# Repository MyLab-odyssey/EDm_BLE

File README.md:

# EDm_BLE

Monitor the status of your Smart electric drive EV with the Blynk app.  
**This is a work-in-progress project - more features to come...**

Further documentation in the [Wiki](https://github.com/MyLab-odyssey/EDm_BLE/wiki).

---
## Intention
When driving your electric car the knowledge of the real state of charge (SoC) is essential. The usable range is directly related to the SoC of the battery. Some EVs - like the Smart ED - will hide some Ah for back-up and the displayed SoC is more pessimistic than the real charge would suggest.

In the [ED_BMSdiag project](https://github.com/MyLab-odyssey/ED_BMSdiag) I developed a diagnostics tool for the Smart electric drive EV based on an Arduino UNO with a CAN bus shield. Data is send via a serial USB connection to a laptop.  
In every day use this is not a practical use case, so I searched for an easy solution to display the data on a mobile phone. [The Blynk app](http://www.blynk.cc) is a great way for a very flexible dashboard on iOS and on Android phones.

<p align="center">

<p/>

You can display the content you need and arrange different widgets to show the values. Using gauges, value displays and graphs the app gives you the freedom to select the data you really need.

<p align="center">

<br>
(rearrange widgets or add a graph)<br>
<p/>

Blynk is able to use a bluetooth low energy connection for data transmission. But adding a BLE interface to the Arduino would be only a small step forward. So I decided to develop my own BLE dongle to connect to the OBD port of the car. A system I can leave plugged in while driving and to be energy efficient to stay without depleting the 12V battery. Therefor the RFduino micro controller is the perfect fit as it is small, very efficient and stable. It runs a well developed RTOS and can be programmed with the Arduino IDE. It has excellent ultra low power features for a deep sleep of the module.

## What is Needed
* The PCB: You can use the Eagle CAD files for ordering the PCB at various online manufacturing services. You will find the board on [OSH Park and can order it there](https://oshpark.com/shared_projects/RnRzi1Kz). As an alternative a local FabLab or MakerSpace may has a rapid prototyping mill for PCBs you could use. I made my prototype this way.

* The parts: get the complete bill of materials ([BOM](https://github.com/MyLab-odyssey/EDm_BLE/blob/master/schematics/EDm_v1.1_BOM.txt)) from my GitHub-repo. Most parts are stock articles from common distributors.
You need skills in soldering SMD parts and a good soldering station (the CAN controller is fine pitch).

## Getting started
* Install the [Arduino IDE](https://www.arduino.cc/en/Main/Software) and then follow the instructions for [RFduino installation](https://github.com/RFduino/RFduino/blob/master/README.md#installation).
* Download the Repo and copy it to your Arduino folder. Find detailed instructions in my ED_BMSdiag project ([english](https://github.com/MyLab-odyssey/ED_BMSdiag/wiki/Installation) | [german](https://github.com/MyLab-odyssey/ED_BMSdiag/wiki/Installation_DE)), as it is very similar.
* Using Blynk is described in the Wiki. You can clone my basic project and then modify it. The access token must be copied into the program code and is then compiled for the RFduino.
* Connect the USB to UART adapter and upload the program.
* Remove the USB programmer and plug the dongle into the OBD port of the car. Start Blynk app and connect to the dongle (detailed instructions here).

## Outlook
Currently only live data will be displayed. I will try to port the complete features of the ED_BMSdiag project, so you can use Blynk to get all information about your vehicle.

## Version history
version  | comment
-------- | --------
v0.1.0   | Initial commit with all readouts as in the vehicle dashboard.

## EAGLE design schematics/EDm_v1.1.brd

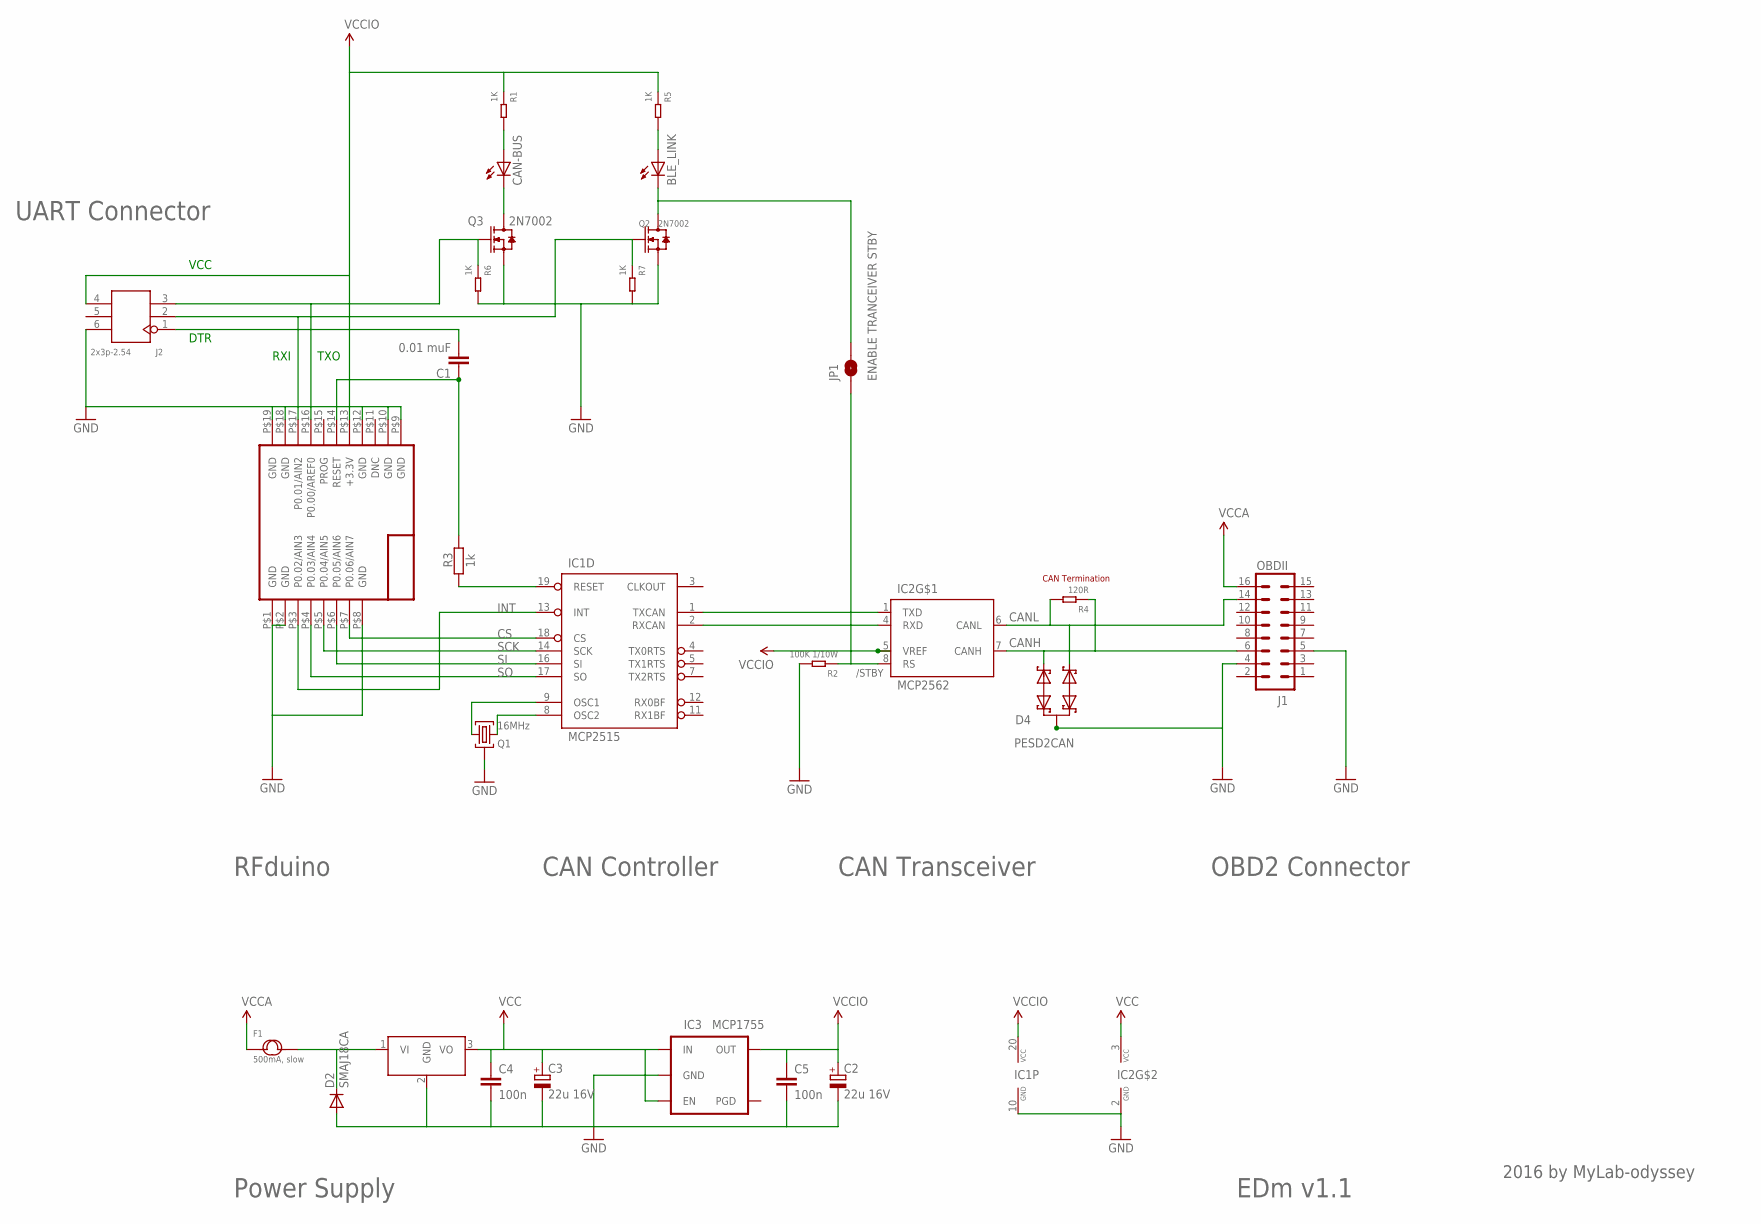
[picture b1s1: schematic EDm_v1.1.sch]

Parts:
78SR: DCDC_OKI-78SR; OKI-78SRH
BLE_LINK: LED_E; LED_1206
C1: 0.01 muF; C0805
C2, C3: 22u 16V; SMC_A
C4, C5: 100n; 0805
CAN-BUS: LED_E; LED_1206
D2: SMAJ18CA; SMA-DIODE
D4: PESD2CAN; SOT23
F1: 500mA, slow; F3366
IC1: MCP2515; TSSOP20
IC2: MCP2562; SO08
IC3: MCP1755; SOT23-5
J1: OBDII; OBDII-COMTECH; PARTNO OBD-II
J2: 2x3p-2.54; H2X3-2.54
JP1: ENABLE TRANCEIVER STBY; PAD-JUMPER-2-NO_YES_SILK
Q1: 16MHz; SMD_OSC_35X15
Q2, Q3: 2N7002; SOT-23
R1, R5, R6, R7: 1K; R0603
R2: 100K 1/10W; R0603
R3: 1k; R0603
R4: 120R; R0603
RFDUINO: RFD22301; RFD21733

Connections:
CANH: D4.1, IC2.7 (CANH), J1.6, R4.1
CANL: D4.2, IC2.6 (CANL), J1.14, R4.2
CAN_RX: IC1.2 (RXCAN), IC2.4 (RXD)
CAN_TX: IC1.1 (TXCAN), IC2.1 (TXD)
CS: IC1.18 (CS), RFDUINO.P$7 (P0.06/AIN7)
GND: 78SR.2 (GND), C2.-, C3.-, C4.2, C5.2, D2.A, D4.3, IC1.10 (GND), IC2.2 (GND), IC3.2 (GND), J1.4, J1.5, J2.6, Q1.GND, Q2.2 (S), Q3.2 (S), R2.2, R6.2, R7.2, RFDUINO.P$1 (GND), RFDUINO.P$2 (GND), RFDUINO.P$8 (GND), RFDUINO.P$9 (GND), RFDUINO.P$10 (GND), RFDUINO.P$12 (GND), RFDUINO.P$18 (GND), RFDUINO.P$19 (GND)
INT: IC1.13 (INT), RFDUINO.P$3 (P0.02/AIN3)
unnamed: IC1.19 (RESET), R3.2
unnamed: C1.1, R3.1, RFDUINO.P$14 (RESET)
unnamed: J2.3, Q3.1 (G), R6.1, RFDUINO.P$16 (P0.00/AREF0)
unnamed: J2.2, Q2.1 (G), R7.1, RFDUINO.P$17 (P0.01/AIN2)
unnamed: C1.2, J2.1
unnamed: CAN-BUS.C, Q3.3 (D)
unnamed: CAN-BUS.A, R1.2
unnamed: BLE_LINK.A, R5.2
unnamed: BLE_LINK.C, JP1.2, Q2.3 (D)
unnamed: IC2.8 (RS), JP1.1, R2.1
unnamed: 78SR.1 (VI), D2.C, F1.2
OSC1: IC1.9 (OSC1), Q1.1
OSC2: IC1.8 (OSC2), Q1.2
SCK: IC1.14 (SCK), RFDUINO.P$5 (P0.04/AIN5)
SI: IC1.16 (SI), RFDUINO.P$6 (P0.05/AIN6)
SO: IC1.17 (SO), RFDUINO.P$4 (P0.03/AIN4)
VCC: 78SR.3 (VO), C3.+, C4.1, IC2.3 (VCC), IC3.1 (IN), IC3.3 (EN)
VCCA: F1.1, J1.16
VCCIO: C2.+, C5.1, IC1.20 (VCC), IC2.5 (VREF), IC3.5 (OUT), J2.4, R1.1, R5.1, RFDUINO.P$13 (+3.3V)

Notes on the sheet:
CAN Termination
CAN Controller
CAN Transceiver
/STBY
OBD2 Connector
RFduino
UART Connector
Power Supply
EDm v1.1
2016 by MyLab-odyssey
VCC
TXO
RXI
DTR

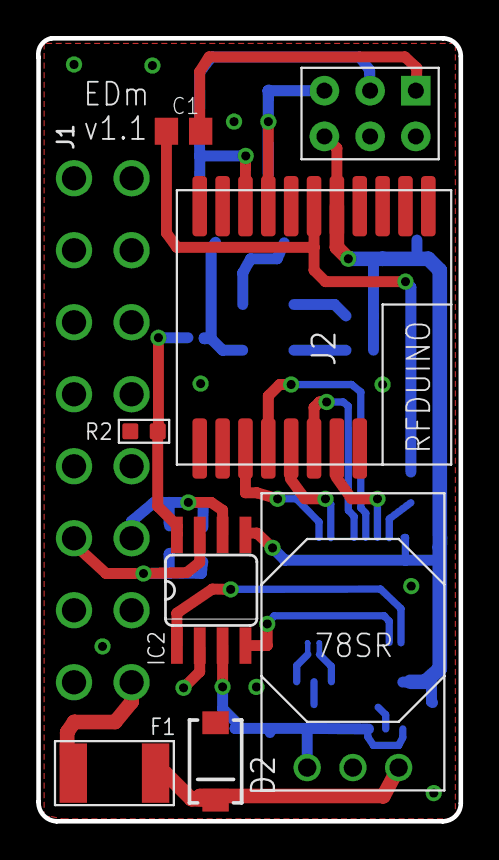
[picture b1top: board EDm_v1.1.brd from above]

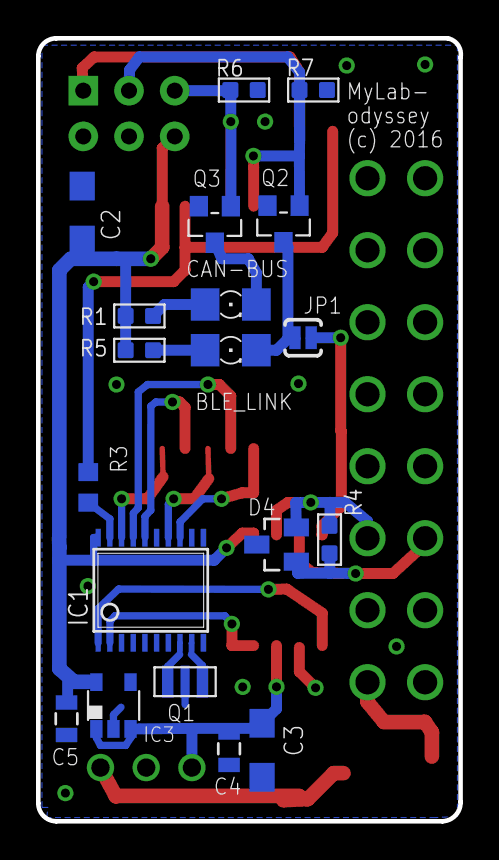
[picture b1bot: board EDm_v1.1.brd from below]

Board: 2 copper layers, 23.5 x 43.5 mm, 28 parts (19 on the bottom side), 26 nets.

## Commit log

2016-11-06 Added link to PCB @OSH park
2018-05-22 Updated BOM as some parts are EOL (end–of–life)
    Alternatives for resonator and RFduino listed.
2018-05-22 EDIT: use 3.3V variant of MCP1755 !
    THX to comment by cdn!
2022-07-26 Update README.md
    #StandWithUkraine - THX Volodymyr Shymanskyy for creating Blynk ;-)

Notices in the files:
README.md:
License: MIT
schematics/EDm_v1.1.brd:
(c) 2016
parts and their libraries:
SparkFun-Capacitors: Licensing: Creative Commons ShareAlike 4.0 International - https://creativecommons.org/licenses/by-sa/4.0
